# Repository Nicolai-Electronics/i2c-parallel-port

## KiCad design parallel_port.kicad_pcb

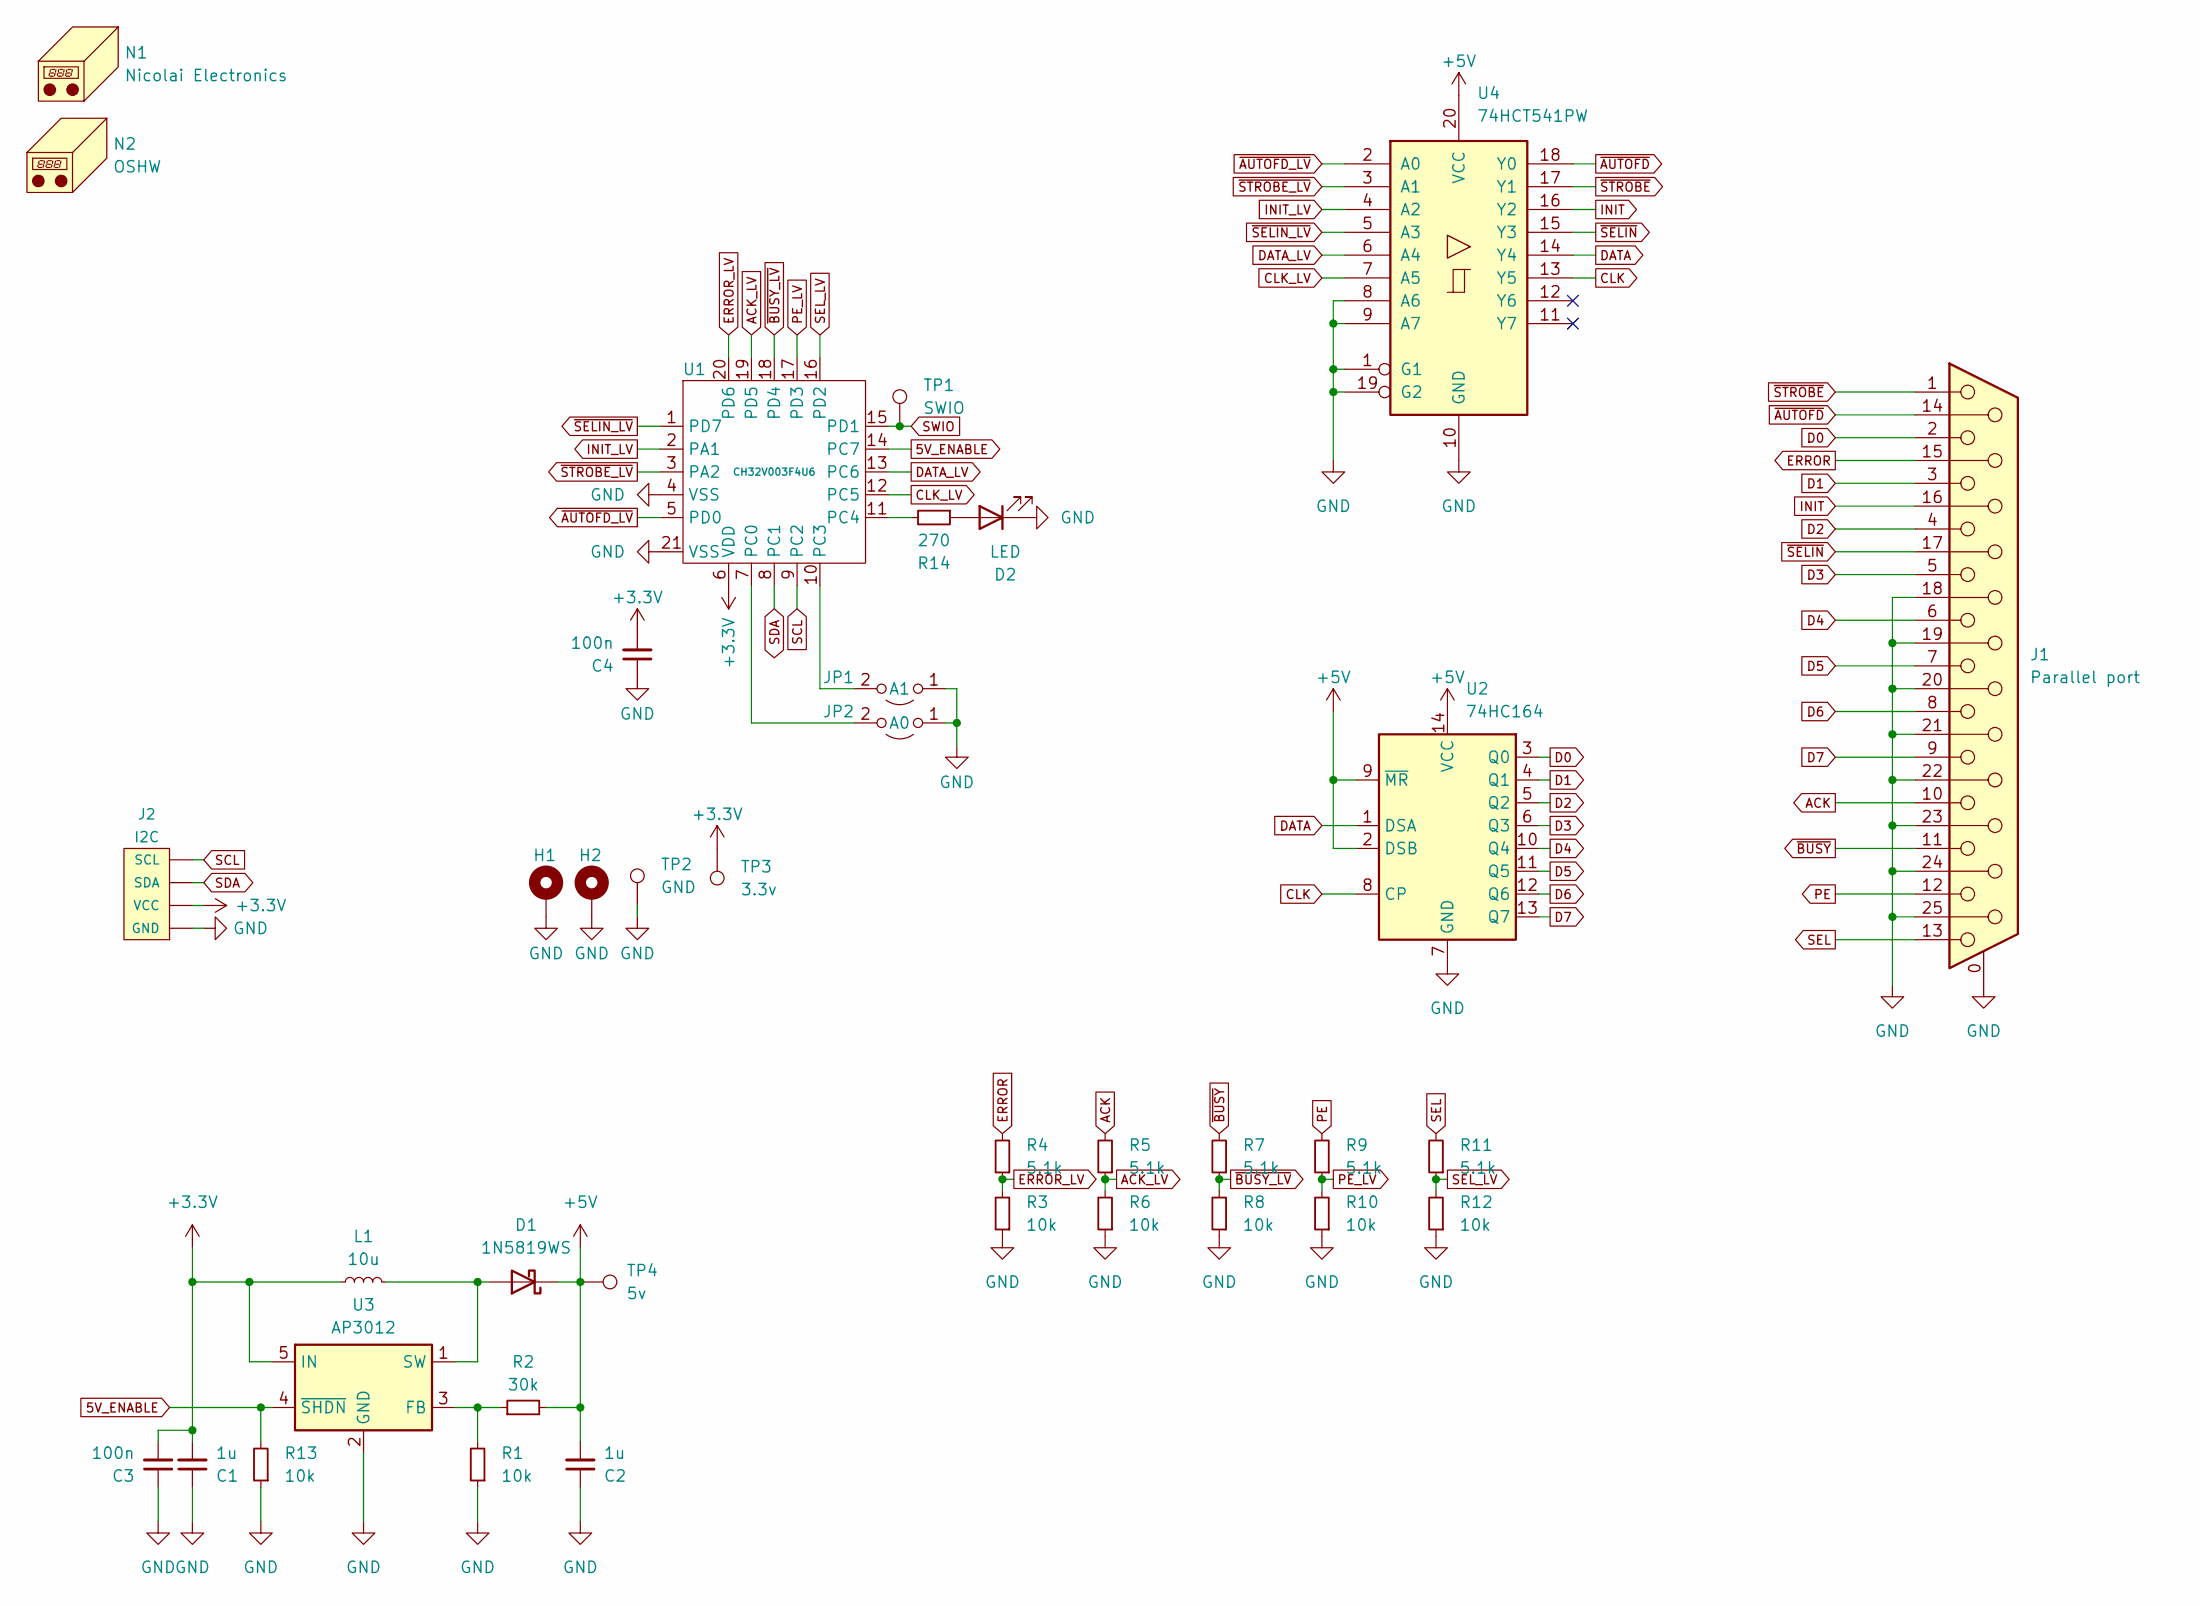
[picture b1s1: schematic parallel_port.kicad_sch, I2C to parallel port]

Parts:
C1, C2: 1u; C_0402_1005Metric
C3, C4: 100n; C_0402_1005Metric
D1: 1N5819WS; D_SOD-323
D2: LED; LED_0603_1608Metric; LCSC C264473
H1, H2: MountingHole_3.2mm_M3_Pad_Via
J1: Parallel port; DSUB-25_Female_Horizontal_P2.77x2.84mm_EdgePinOffset7.70mm_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
J2: I2C; 1X04_1MM_RA_GND; LCSC C160404
JP1: A1; SolderJumper-2_P1.3mm_Open_TrianglePad1.0x1.5mm
JP2: A0; SolderJumper-2_P1.3mm_Open_TrianglePad1.0x1.5mm
L1: 10u; Inductor_MSC20FC; Part Ceaiya CRH201610S-100MT; LCSC C520204
N1: Nicolai Electronics; logo_nicolai
N2: OSHW; OSHW-Logo2_7.3x6mm_Mask
R1, R3, R6, R8, R10, R12, R13: 10k; R_0402_1005Metric
R2: 30k; R_0402_1005Metric
R4, R5, R7, R9, R11: 5.1k; R_0402_1005Metric
R14: 270; R_0402_1005Metric; LCSC C22966
TP1: SWIO; TestPoint_Pad_D2.0mm
TP2: GND; TestPoint_Pad_D2.0mm
TP3: 3.3v; TestPoint_Pad_D2.0mm
TP4: 5v; TestPoint_Pad_D2.0mm
U1: CH32V003F4U6; QFN-20-1EP_3x3mm_P0.4mm_EP1.65x1.65mm; LCSC C5299908
U2: 74HC164; SO-14_3.9x8.65mm_P1.27mm; LCSC C6825
U3: AP3012; SOT-23-5; LCSC C102618
U4: 74HCT541PW; TSSOP-20_4.4x6.5mm_P0.65mm; LCSC C131314

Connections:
5V_ENABLE: R13.2, U1.14 (PC7), U3.4 (~SHDN)
+3.3V: C1.2, C3.2, C4.2, J2.2 (VCC), L1.1, TP3.1, U1.6 (VDD), U3.5 (IN)
+5V: C2.2, D1.1 (K), R2.2, TP4.1, U2.2 (DSB), U2.9 (~MR), U2.14 (VCC), U4.20 (VCC)
ACK: J1.10, R5.2
ACK_LV: R5.1, R6.2, U1.19 (PD5)
CLK: U2.8 (CP), U4.13 (Y5)
CLK_LV: U1.12 (PC5), U4.7 (A5)
D0: J1.2, U2.3 (Q0)
D1: J1.3, U2.4 (Q1)
D2: J1.4, U2.5 (Q2)
D3: J1.5, U2.6 (Q3)
D4: J1.6, U2.10 (Q4)
D5: J1.7, U2.11 (Q5)
D6: J1.8, U2.12 (Q6)
D7: J1.9, U2.13 (Q7)
DATA: U2.1 (DSA), U4.14 (Y4)
DATA_LV: U1.13 (PC6), U4.6 (A4)
ERROR: J1.15, R4.2
ERROR_LV: R3.2, R4.1, U1.20 (PD6)
GND: C1.1, C2.1, C3.1, C4.1, D2.1 (K), H1.1, H2.1, J1.0 (PAD), J1.18, J1.19, J1.20, J1.21, J1.22, J1.23, J1.24, J1.25, J2.1 (GND), J2.5, J2.6, JP1.1 (A), JP2.1 (A), R1.1, R3.1, R6.1, R8.1, R10.1, R12.1, R13.1, TP2.1, U1.4 (VSS), U1.21 (VSS), U2.7 (GND), U3.2 (GND), U4.1 (G1), U4.8 (A6), U4.9 (A7), U4.10 (GND), U4.19 (G2)
INIT: J1.16, U4.16 (Y2)
INIT_LV: U1.2 (PA1), U4.4 (A2)
unnamed: D1.2 (A), L1.2, U3.1 (SW)
unnamed: D2.2 (A), R14.1
unnamed: JP1.2 (B), U1.10 (PC3)
unnamed: JP2.2 (B), U1.7 (PC0)
unnamed: R14.2, U1.11 (PC4)
unnamed: R1.2, R2.1, U3.3 (FB)
PE: J1.12, R9.2
PE_LV: R9.1, R10.2, U1.17 (PD3)
SCL: J2.4 (SCL), U1.9 (PC2)
SDA: J2.3 (SDA), U1.8 (PC1)
SEL: J1.13, R11.2
SEL_LV: R11.1, R12.2, U1.16 (PD2)
SWIO: TP1.1, U1.15 (PD1)
~AUTOFD_LV: U1.5 (PD0), U4.2 (A0)
~AUTOFD: J1.14, U4.18 (Y0)
~BUSY_LV: R7.1, R8.2, U1.18 (PD4)
~BUSY: J1.11, R7.2
~SELIN_LV: U1.1 (PD7), U4.5 (A3)
~SELIN: J1.17, U4.15 (Y3)
~STROBE_LV: U1.3 (PA2), U4.3 (A1)
~STROBE: J1.1, U4.17 (Y1)

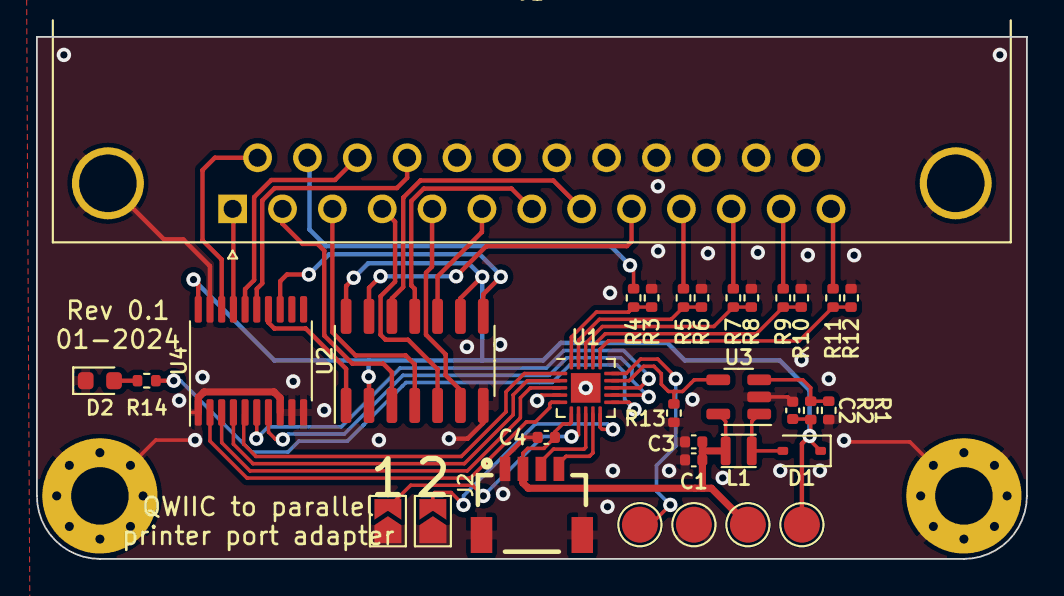
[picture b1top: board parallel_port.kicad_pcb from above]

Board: 2 copper layers, 55.0 x 29.0 mm, 37 parts (1 on the bottom side), 43 nets.
